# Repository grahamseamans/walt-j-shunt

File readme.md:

https://refsnregs.waltjung.org/The_PM829_Reference.pdf
https://refsnregs.waltjung.org/UnivReg_122714_121718c.pdf

shunt reg from the generous walt jung

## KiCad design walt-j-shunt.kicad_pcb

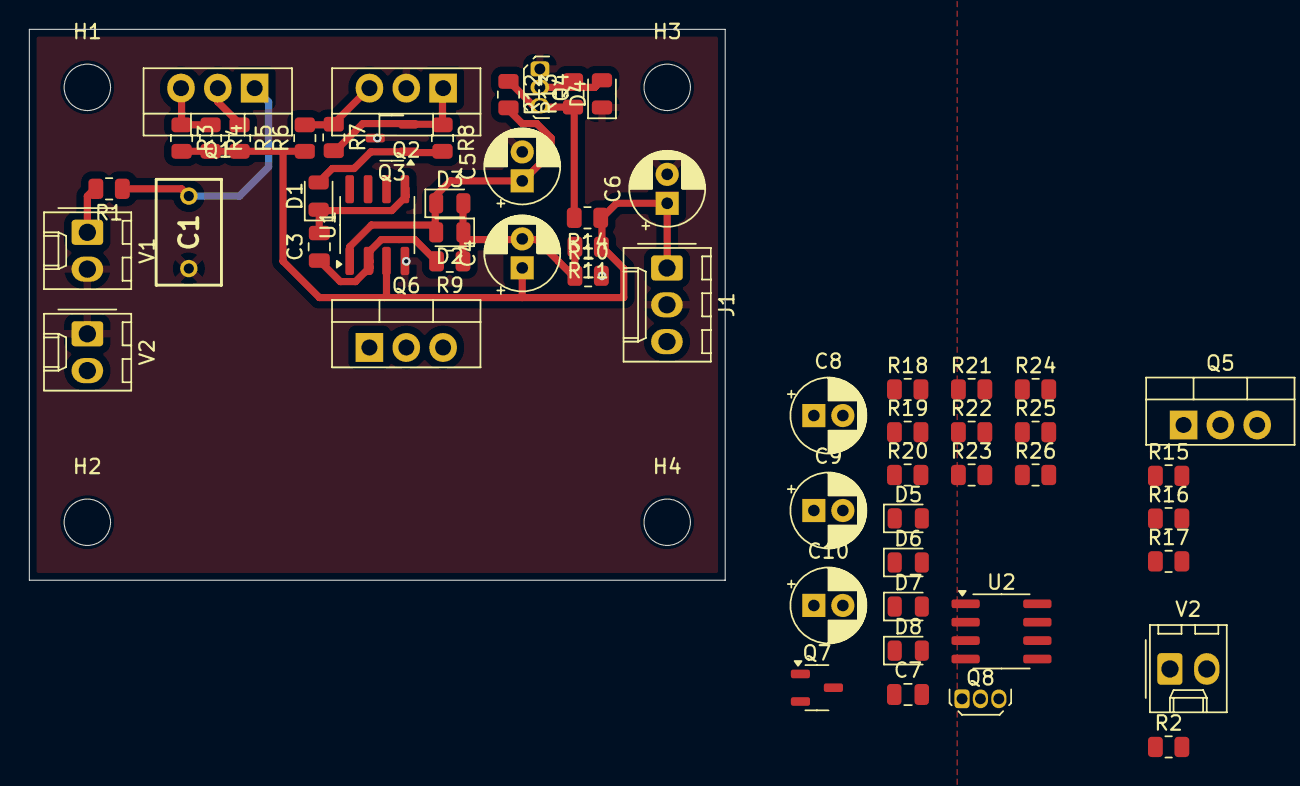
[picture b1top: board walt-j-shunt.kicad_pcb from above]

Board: 2 copper layers, 48.0 x 38.0 mm, 61 parts (0 on the bottom side), 29 nets.

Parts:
C1: 1uf; B32529C105J
C3, C7: 33pf; C_0805_2012Metric
C4, C5, C6, C8, C9, C10: 100uf; CP_Radial_D5.0mm_P2.00mm
D1, D5: rled; D_0805_2012Metric
D2, D3, D6, D7: D; D_0805_2012Metric
D4, D8: gled; LED_0805_2012Metric
H1, H2, H3, H4: MountingHole; MountingHole_3.2mm_M3_ISO7380
J1: Screw_Terminal_01x03; Molex_KK-254_AE-6410-03A_1x03_P2.54mm_Vertical
Q1, Q5: DN2540; TO-220-3_Vertical
Q2, Q6: D45H11G; TO-220-3_Vertical
Q3, Q7: MMBT2907AL; SOT-23-3
Q4, Q8: ZTX951; TO-92Flat
R1, R2, R6, R18: 1r; R_0805_2012Metric
R3, R4, R15, R16: 20r; R_0805_2012Metric
R5, R17: 100r; R_0805_2012Metric
R7, R19: 50r; R_0805_2012Metric
R8, R20: 221r; R_0805_2012Metric
R9, R21: 475; R_0805_2012Metric
R10, R22: 500r; R_0805_2012Metric
R11, R23: 2k; R_0805_2012Metric
R12, R24: 1k; R_0805_2012Metric
R13, R25: 150r; R_0805_2012Metric
R14, R26: 1.8k; R_0805_2012Metric
U1, U2: AD817; SOIC-8_3.9x4.9mm_P1.27mm
V1, V2, V2#2: VSIN; Molex_KK-254_AE-6410-02A_1x02_P2.54mm_Vertical

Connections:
/current_source1/+: R2.1, R15.2, R16.2, R17.2
/current_source1/m_g: Q5.2 (G), R17.1
/current_source/m_g: Q1.2 (G), R5.1
/reg1/v-ref: Q8.3 (E), R24.1, R25.1, R26.2
/reg/v-ref: Q4.3 (E), R12.1, R13.1, R14.2
GND: C1.2, C5.2, C6.2, C8.1, C10.1, D4.1 (K), J1.2, Q2.2 (C), Q3.3 (C), Q4.1 (C), R10.2, R18.1, R23.1, R26.1, U1.4 (V-), U2.3 (V+), V1.2, V2.1, V2#2.1
unnamed: D1.2 (A), Q3.1 (B), R8.2
unnamed: C3.2, D1.1 (K), U1.5
unnamed: C5.1, D2.2 (A), D3.1 (K), R12.2, U1.1 (+)
unnamed: C4.2, D2.1 (K), D3.2 (A), R9.1, R10.1, R11.2
unnamed: D4.2 (A), Q4.2 (B), R13.2
unnamed: D5.2 (A), Q7.1 (B), R20.2
unnamed: C7.2, D5.1 (K), U2.5
unnamed: C9.1, D6.2 (A), D7.1 (K), R24.2, U2.1 (+)
unnamed: C8.2, D6.1 (K), D7.2 (A), R21.1, R22.1, R23.2
unnamed: D8.2 (A), Q8.2 (B), R25.2
unnamed: Q1.3 (S), R3.1, R4.1
unnamed: Q2.1 (B), Q3.2 (E), R7.2, R8.1
unnamed: Q2.3 (E), R6.2, R7.1
unnamed: Q5.3 (S), R15.1, R16.1
unnamed: Q6.1 (B), Q7.2 (E), R19.2, R20.1
unnamed: Q6.3 (E), R18.2, R19.1
unnamed: R2.2, V2#2.2
unnamed: C3.1, R9.2, U1.2 (-)
unnamed: C7.1, R21.2, U2.2 (-)
bank-plus: R1.2, V1.1
neg_reg_out: C9.2, C10.2, D8.1 (K), J1.3, Q5.1 (D), Q6.2 (C), Q7.3 (C), Q8.1 (C), R22.2, U2.4 (V-)
pos_reg_out: C4.1, C6.1, J1.1, R3.2, R4.2, R5.2, R6.1, R11.1, R14.1, U1.3 (V+)
pre-cur: C1.1, Q1.1 (D), R1.1

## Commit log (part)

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2025-01-04 added satic pdfs and mini readme
2025-01-04 footprint placeholders
2025-01-04 basic layout positive
2025-01-04 remove cache from git
2025-01-04 plus only, cap and rectififer on board
2025-01-05 working in subsheet
2025-01-05 bipolar. untested
2025-01-07 pretty neat neg needs testing
